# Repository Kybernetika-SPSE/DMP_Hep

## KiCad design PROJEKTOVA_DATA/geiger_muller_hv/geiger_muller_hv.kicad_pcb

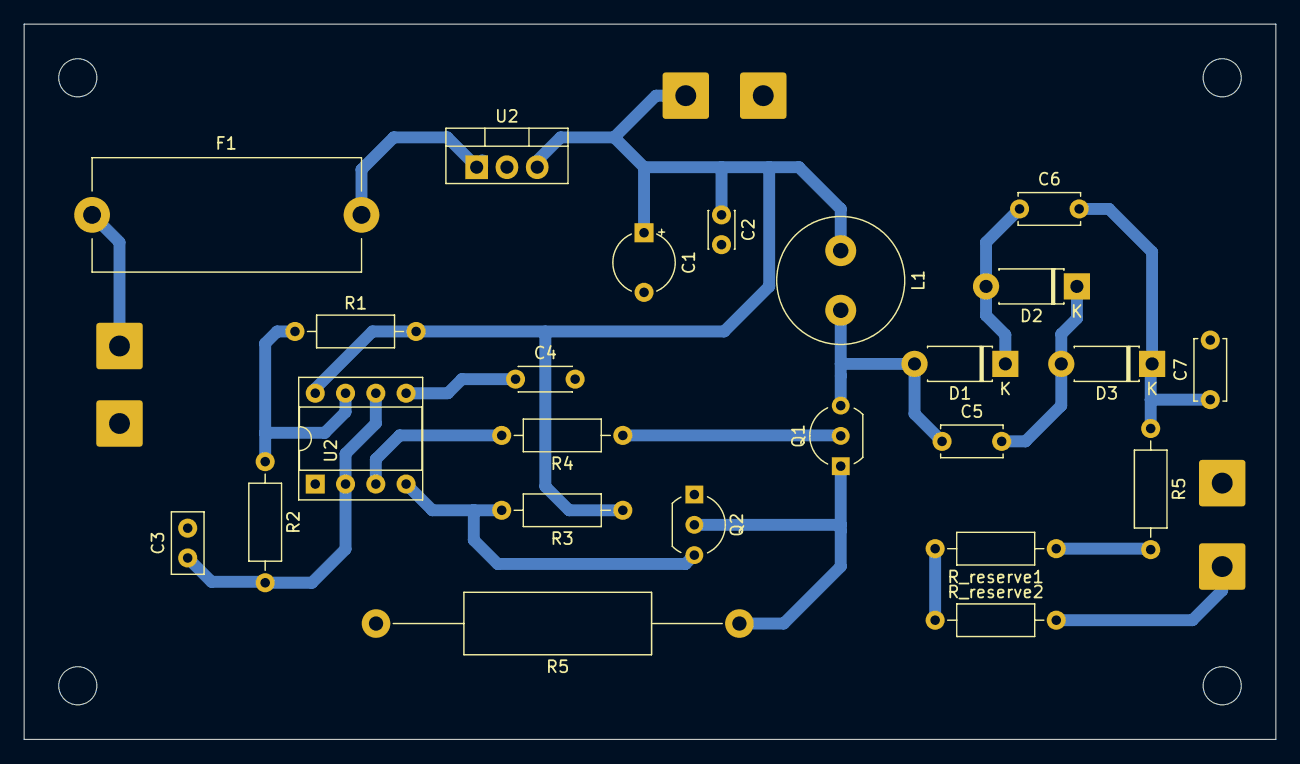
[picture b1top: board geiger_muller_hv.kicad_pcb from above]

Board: 2 copper layers, 105.0 x 60.0 mm, 34 parts (0 on the bottom side), 18 nets.

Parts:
C1: 100uF; CP_Radial_Tantal_D5.0mm_P5.00mm
C2: 100nF; C_Disc_D3.0mm_W2.0mm_P2.50mm
C3: 1nF; C_Disc_D5.0mm_W2.5mm_P2.50mm
C4: 100nF; C_Disc_D4.3mm_W1.9mm_P5.00mm
C5, C6, C7: 10nF; C_Disc_D5.0mm_W2.5mm_P5.00mm
D1, D2, D3: 1N4937; D_DO-41_SOD81_P7.62mm_Horizontal
F1: Fuse; Fuseholder_Cylinder-5x20mm_Stelvio-Kontek_PTF78_Horizontal_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
H1, H2, H3, H4: MountingHole; MountingHole_3.2mm_M3
J1, J2, J3, J4, J5, J6: Conn_01x01_Pin; SolderWire-1sqmm_1x01_D1.4mm_OD3.9mm
L1: 10mH; L_Radial_D10.5mm_P5.00mm_Abacron_AISR-01
Q1: MPSA42; TO-92_Inline_Wide
Q2: 2N3904; TO-92_Inline_Wide
R1, R2: 33k; R_Axial_DIN0207_L6.3mm_D2.5mm_P10.16mm_Horizontal
R3: 100k; R_Axial_DIN0207_L6.3mm_D2.5mm_P10.16mm_Horizontal
R4: 3k; R_Axial_DIN0207_L6.3mm_D2.5mm_P10.16mm_Horizontal
R5: 7M5; R_Axial_DIN0207_L6.3mm_D2.5mm_P10.16mm_Horizontal
R5#2: 27R; R_Axial_DIN0516_L15.5mm_D5.0mm_P30.48mm_Horizontal
R_reserve1, R_reserve2: 7M5; R_Axial_DIN0207_L6.3mm_D2.5mm_P10.16mm_Horizontal
U2: NE555P; DIP-8_W7.62mm_Socket
U2#2: L7805; TO-220-3_Vertical

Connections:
+5V: F1.1, J1.1
GND: C1.2, C2.2, C3.2, C4.2, C7.2, J3.1, J4.1, J6.1, Q2.1 (E), R5#2.2, U2.1 (GND), U2#2.2 (GND)
unnamed: C5.1, D1.2 (A), L1.2, Q1.3 (C)
unnamed: C6.1, D1.1 (K), D2.2 (A)
unnamed: C5.2, D2.1 (K), D3.2 (A)
unnamed: C6.2, C7.1, D3.1 (K), R5.1
unnamed: J2.1, R_reserve2.2
unnamed: C1.1, C2.1, J5.1, L1.1, R1.2, R3.1, U2.8 (VCC), U2#2.3 (OUT)
unnamed: Q1.1 (E), Q2.2 (B), R5#2.1
unnamed: Q2.3 (C), R3.2, U2.4 (R)
unnamed: Q1.2 (B), R4.1
unnamed: R5.2, R_reserve1.1
unnamed: R_reserve1.2, R_reserve2.1
unnamed: C4.1, U2.5 (CV)
unnamed: R1.1, R2.1, U2.7 (DIS)
unnamed: R4.2, U2.3 (Q)
unnamed: C3.1, R2.2, U2.2 (TR), U2.6 (THR)
unnamed: F1.2, U2#2.1 (IN)

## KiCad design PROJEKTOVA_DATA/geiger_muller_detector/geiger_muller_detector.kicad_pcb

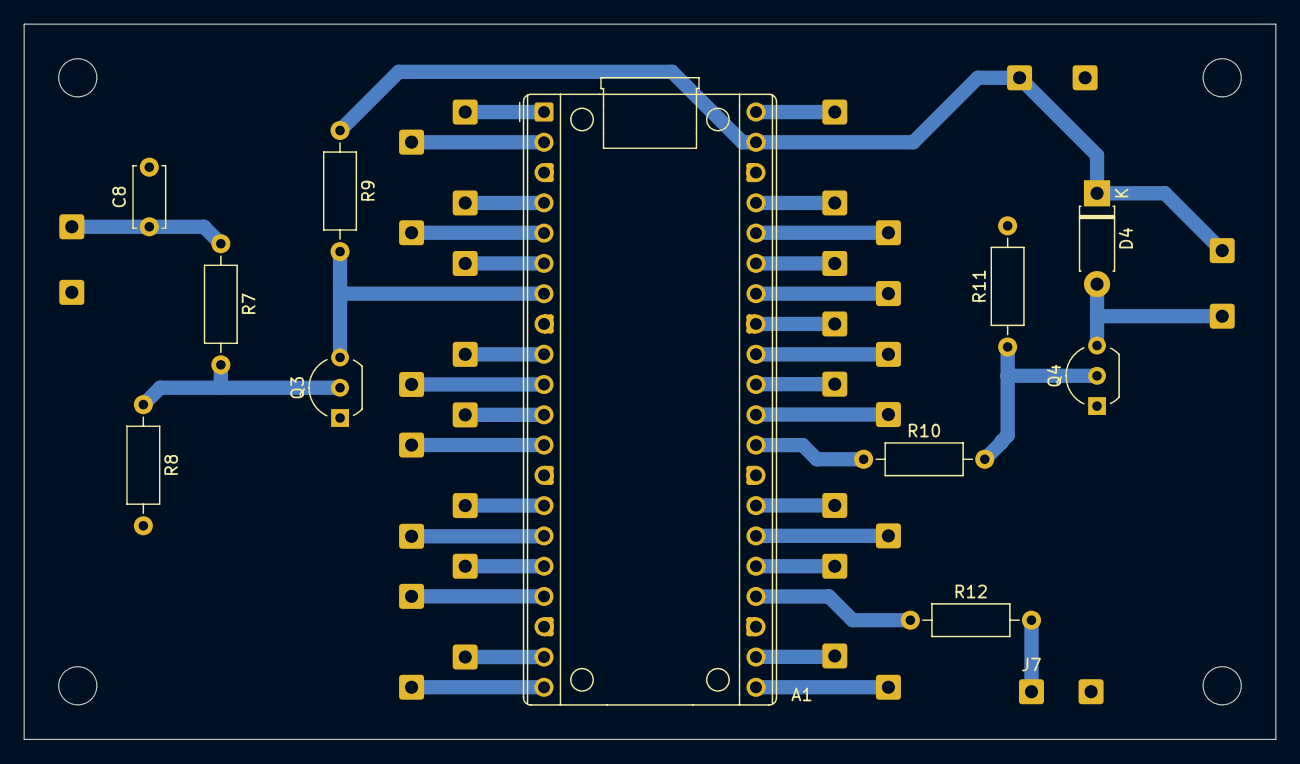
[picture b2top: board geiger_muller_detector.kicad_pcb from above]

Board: 2 copper layers, 105.0 x 60.0 mm, 52 parts (0 on the bottom side), 37 nets.

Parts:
A1: RaspberryPi_Pico; RaspberryPi_Pico_Common_THT
C8: 270pF; C_Disc_D5.0mm_W2.5mm_P5.00mm
D4: 1N4937; D_DO-41_SOD81_P7.62mm_Horizontal
H1, H2, H3, H4: MountingHole; MountingHole_3.2mm_M3
J1, J2, J3, J4, J5, J6, J7, J8, J9, J10, J11, J12, J12#2, J13, J14, J15, J16, J17, J18, J19, J20, J21, J21#2, J23, J24, J25, J26, J28, J29, J30, J31, J32, J33, J34, J35, J36, J37: Conn_01x01_Pin; SolderWire-0.5sqmm_1x01_D0.9mm_OD2.1mm
Q3, Q4: 2N3904; TO-92_Inline_Wide
R7: 10k; R_Axial_DIN0207_L6.3mm_D2.5mm_P10.16mm_Horizontal
R8: 470k; R_Axial_DIN0207_L6.3mm_D2.5mm_P10.16mm_Horizontal
R9: 47k; R_Axial_DIN0207_L6.3mm_D2.5mm_P10.16mm_Horizontal
R10, R11: 1k; R_Axial_DIN0207_L6.3mm_D2.5mm_P10.16mm_Horizontal
R12: 56k; R_Axial_DIN0207_L6.3mm_D2.5mm_P10.16mm_Horizontal

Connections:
+5V: A1.39 (VSYS), D4.1 (K), J2.1, J5.1, R9.1
GND: A1.3 (GND), A1.8 (GND), A1.13 (GND), A1.18 (GND), A1.23 (GND), A1.28 (GND), A1.38 (GND), C8.2, J3.1, J4.1, J8.1, Q3.1 (E), Q4.1 (E), R8.2, R11.2
unnamed: A1.36 (3V3), J37.1
unnamed: A1.37 (3V3_EN), J9.1
unnamed: A1.35 (ADC_VREF), J31.1
unnamed: A1.33 (AGND), J35.1
unnamed: A1.1 (GPIO0), J25.1
unnamed: A1.2 (GPIO1), J24.1
unnamed: A1.4 (GPIO2), J23.1
unnamed: A1.6 (GPIO4), J21#2.1
unnamed: A1.7 (GPIO5), Q3.3 (C), R9.2
unnamed: A1.9 (GPIO6), J20.1
unnamed: A1.10 (GPIO7), J19.1
unnamed: A1.11 (GPIO8), J18.1
unnamed: A1.12 (GPIO9), J17.1
unnamed: A1.14 (GPIO10), J16.1
unnamed: A1.15 (GPIO11), J15.1
unnamed: A1.16 (GPIO12), J14.1
unnamed: A1.17 (GPIO13), J13.1
unnamed: A1.19 (GPIO14), J12#2.1
unnamed: A1.20 (GPIO15), J11.1
unnamed: A1.21 (GPIO16), J26.1
unnamed: A1.24 (GPIO18), R12.1
unnamed: A1.25 (GPIO19), J28.1
unnamed: A1.26 (GPIO20), J29.1
unnamed: A1.27 (GPIO21), J30.1
unnamed: A1.29 (GPIO22), R10.1
unnamed: A1.31 (GPIO26_ADC0), J32.1
unnamed: A1.32 (GPIO27_ADC1), J33.1
unnamed: A1.34 (GPIO28_ADC2), J34.1
unnamed: A1.30 (RUN), J10.1
unnamed: A1.40 (VBUS), J36.1
unnamed: D4.2 (A), J6.1, Q4.3 (C)
unnamed: C8.1, J1.1, R7.1
unnamed: J7.1, R12.2
unnamed: Q3.2 (B), R7.2, R8.1
unnamed: Q4.2 (B), R10.2, R11.1

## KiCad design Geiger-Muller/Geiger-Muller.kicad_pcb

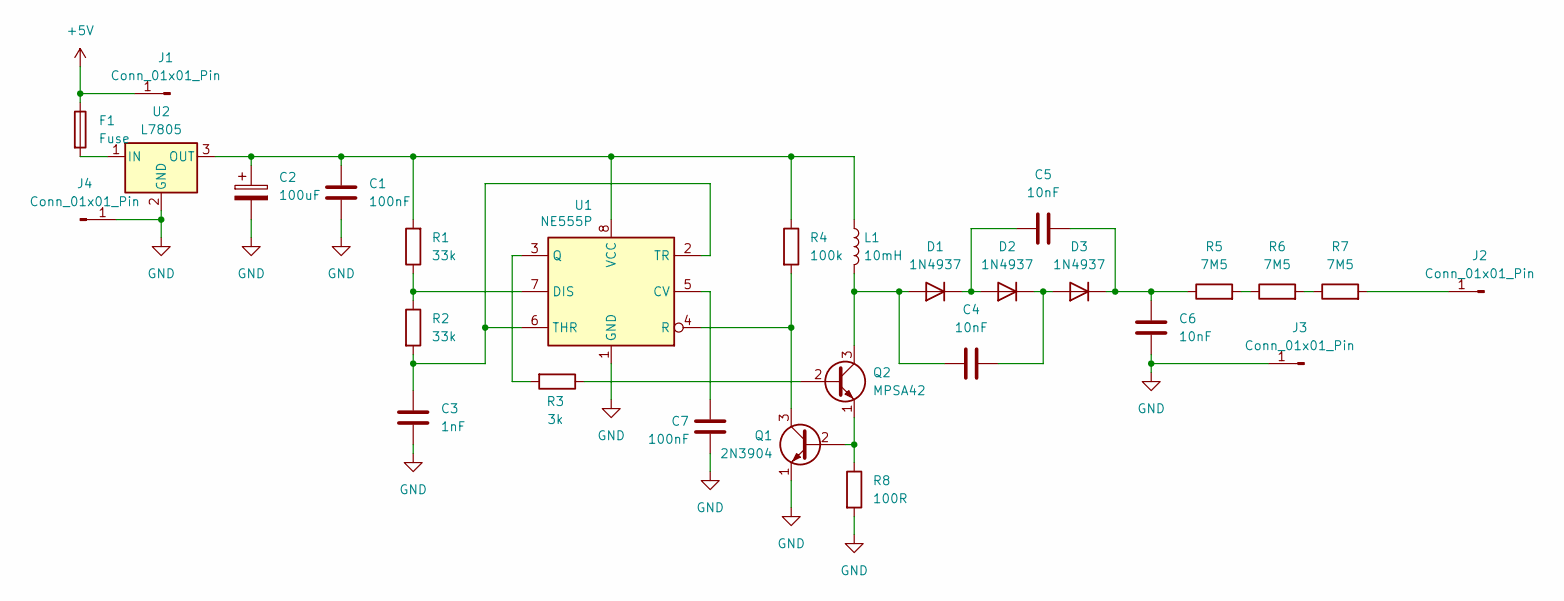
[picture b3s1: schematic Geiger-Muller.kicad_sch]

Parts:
C1: 100nF; C_Disc_D3.0mm_W2.0mm_P2.50mm
C2: 100uF; CP_Radial_Tantal_D5.0mm_P5.00mm
C3: 1nF; C_Disc_D5.0mm_W2.5mm_P2.50mm
C4, C5, C6: 10nF; C_Disc_D5.0mm_W2.5mm_P5.00mm
C7: 100nF; C_Disc_D4.3mm_W1.9mm_P5.00mm
D1, D2, D3: 1N4937; D_DO-41_SOD81_P7.62mm_Horizontal
F1: Fuse; Fuseholder_Cylinder-5x20mm_Stelvio-Kontek_PTF78_Horizontal_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
J1, J2, J3, J4: Conn_01x01_Pin; SolderWire-1sqmm_1x01_D1.4mm_OD3.9mm
L1: 10mH; L_Radial_D10.5mm_P5.00mm_Abacron_AISR-01
Q1: 2N3904; TO-92_Inline_Wide
Q2: MPSA42; TO-92_Inline_Wide
R1, R2: 33k; R_Axial_DIN0207_L6.3mm_D2.5mm_P10.16mm_Horizontal
R3: 3k; R_Axial_DIN0207_L6.3mm_D2.5mm_P10.16mm_Horizontal
R4: 100k; R_Axial_DIN0207_L6.3mm_D2.5mm_P10.16mm_Horizontal
R5, R6, R7: 7M5; R_Axial_DIN0207_L6.3mm_D2.5mm_P10.16mm_Horizontal
R8: 100R; R_Axial_DIN0516_L15.5mm_D5.0mm_P30.48mm_Horizontal
U1: NE555P; DIP-8_W7.62mm_Socket
U2: L7805; TO-220-3_Vertical

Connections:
+5V: F1.1, J1.1
GND: C1.2, C2.2, C3.2, C6.2, C7.2, J3.1, J4.1, Q1.1 (E), R8.2, U1.1 (GND), U2.2 (GND)
unnamed: C4.1, D1.2 (A), L1.2, Q2.3 (C)
unnamed: C5.1, D1.1 (K), D2.2 (A)
unnamed: C4.2, D2.1 (K), D3.2 (A)
unnamed: C5.2, C6.1, D3.1 (K), R5.1
unnamed: J2.1, R7.2
unnamed: Q1.2 (B), Q2.1 (E), R8.1
unnamed: Q1.3 (C), R4.2, U1.4 (R)
unnamed: Q2.2 (B), R3.1
unnamed: R5.2, R6.1
unnamed: R6.2, R7.1
unnamed: C7.1, U1.5 (CV)
unnamed: R1.1, R2.1, U1.7 (DIS)
unnamed: R3.2, U1.3 (Q)
unnamed: C3.1, R2.2, U1.2 (TR), U1.6 (THR)
unnamed: C1.1, C2.1, L1.1, R1.2, R4.1, U1.8 (VCC), U2.3 (OUT)
unnamed: F1.2, U2.1 (IN)

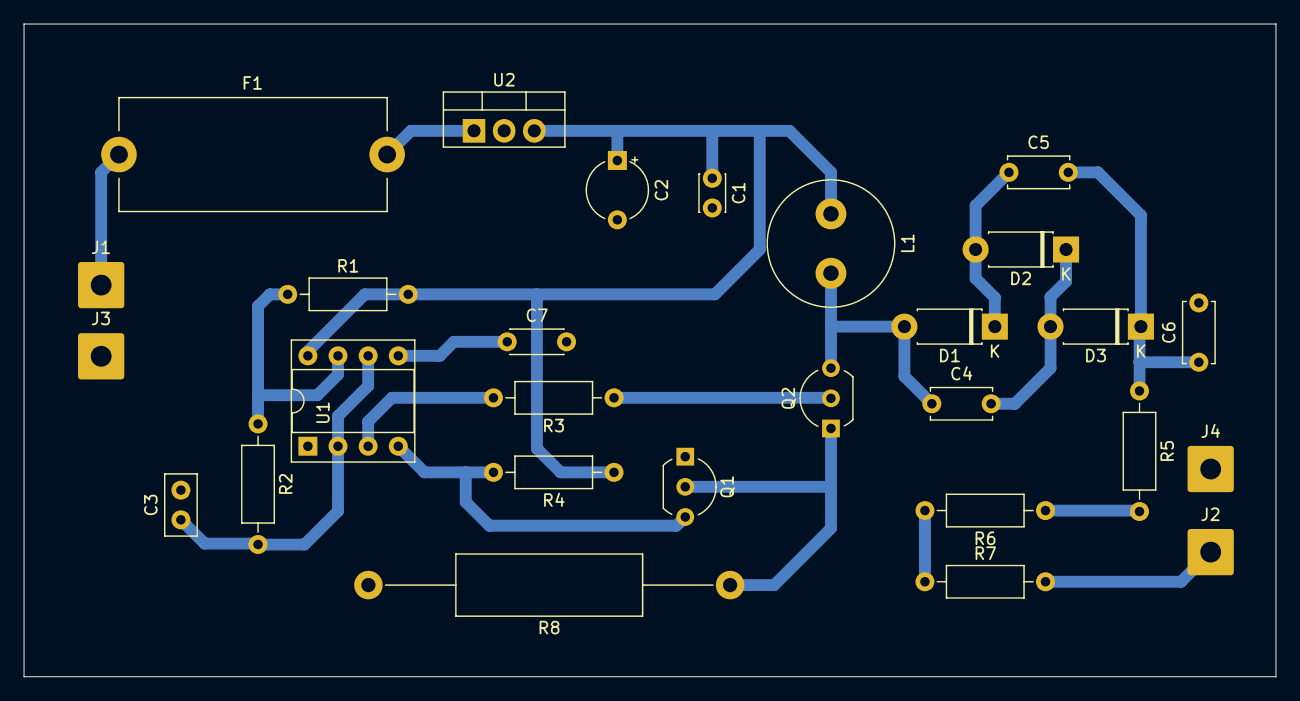
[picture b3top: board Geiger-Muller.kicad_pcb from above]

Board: 2 copper layers, 105.5 x 55.0 mm, 28 parts (0 on the bottom side), 18 nets.

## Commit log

2024-10-30 rijen postup
2024-10-31 dilci vypracovani rijen
2024-11-28 Dilci vypracovani listopad
2024-12-19 odvzdani prosinec
2025-01-06 pcb update
2025-01-20 ungabunga
2025-01-22 main edit
2025-01-23 code fix
2025-02-02 code update and PCB
2025-03-10 dilci vypracovani unor
2025-03-24 hej bejku
2025-04-10 git lab push
2025-04-10 Delete hepm_zadani_DMP.pdf
    fgfg
2025-04-10 Delete samples.xlsx
    delete
2025-04-10 Delete main.py
    delete
2025-04-10 Delete GeigerCounter.ipj.lnk
    delete
2025-04-10 Delete geiger_muller_detector directory
    delete
2025-04-10 Delete geiger_muller_hv directory
    delete
2025-04-10 Delete GeigerCounter directory
    delete
2025-04-10 Delete Dilci_vypracovani directory
    delete
2025-04-10 Delete prilohy directory
    delete
2025-04-10 Delete projektova_data directory
    delete
2025-04-10 zkurveny git
